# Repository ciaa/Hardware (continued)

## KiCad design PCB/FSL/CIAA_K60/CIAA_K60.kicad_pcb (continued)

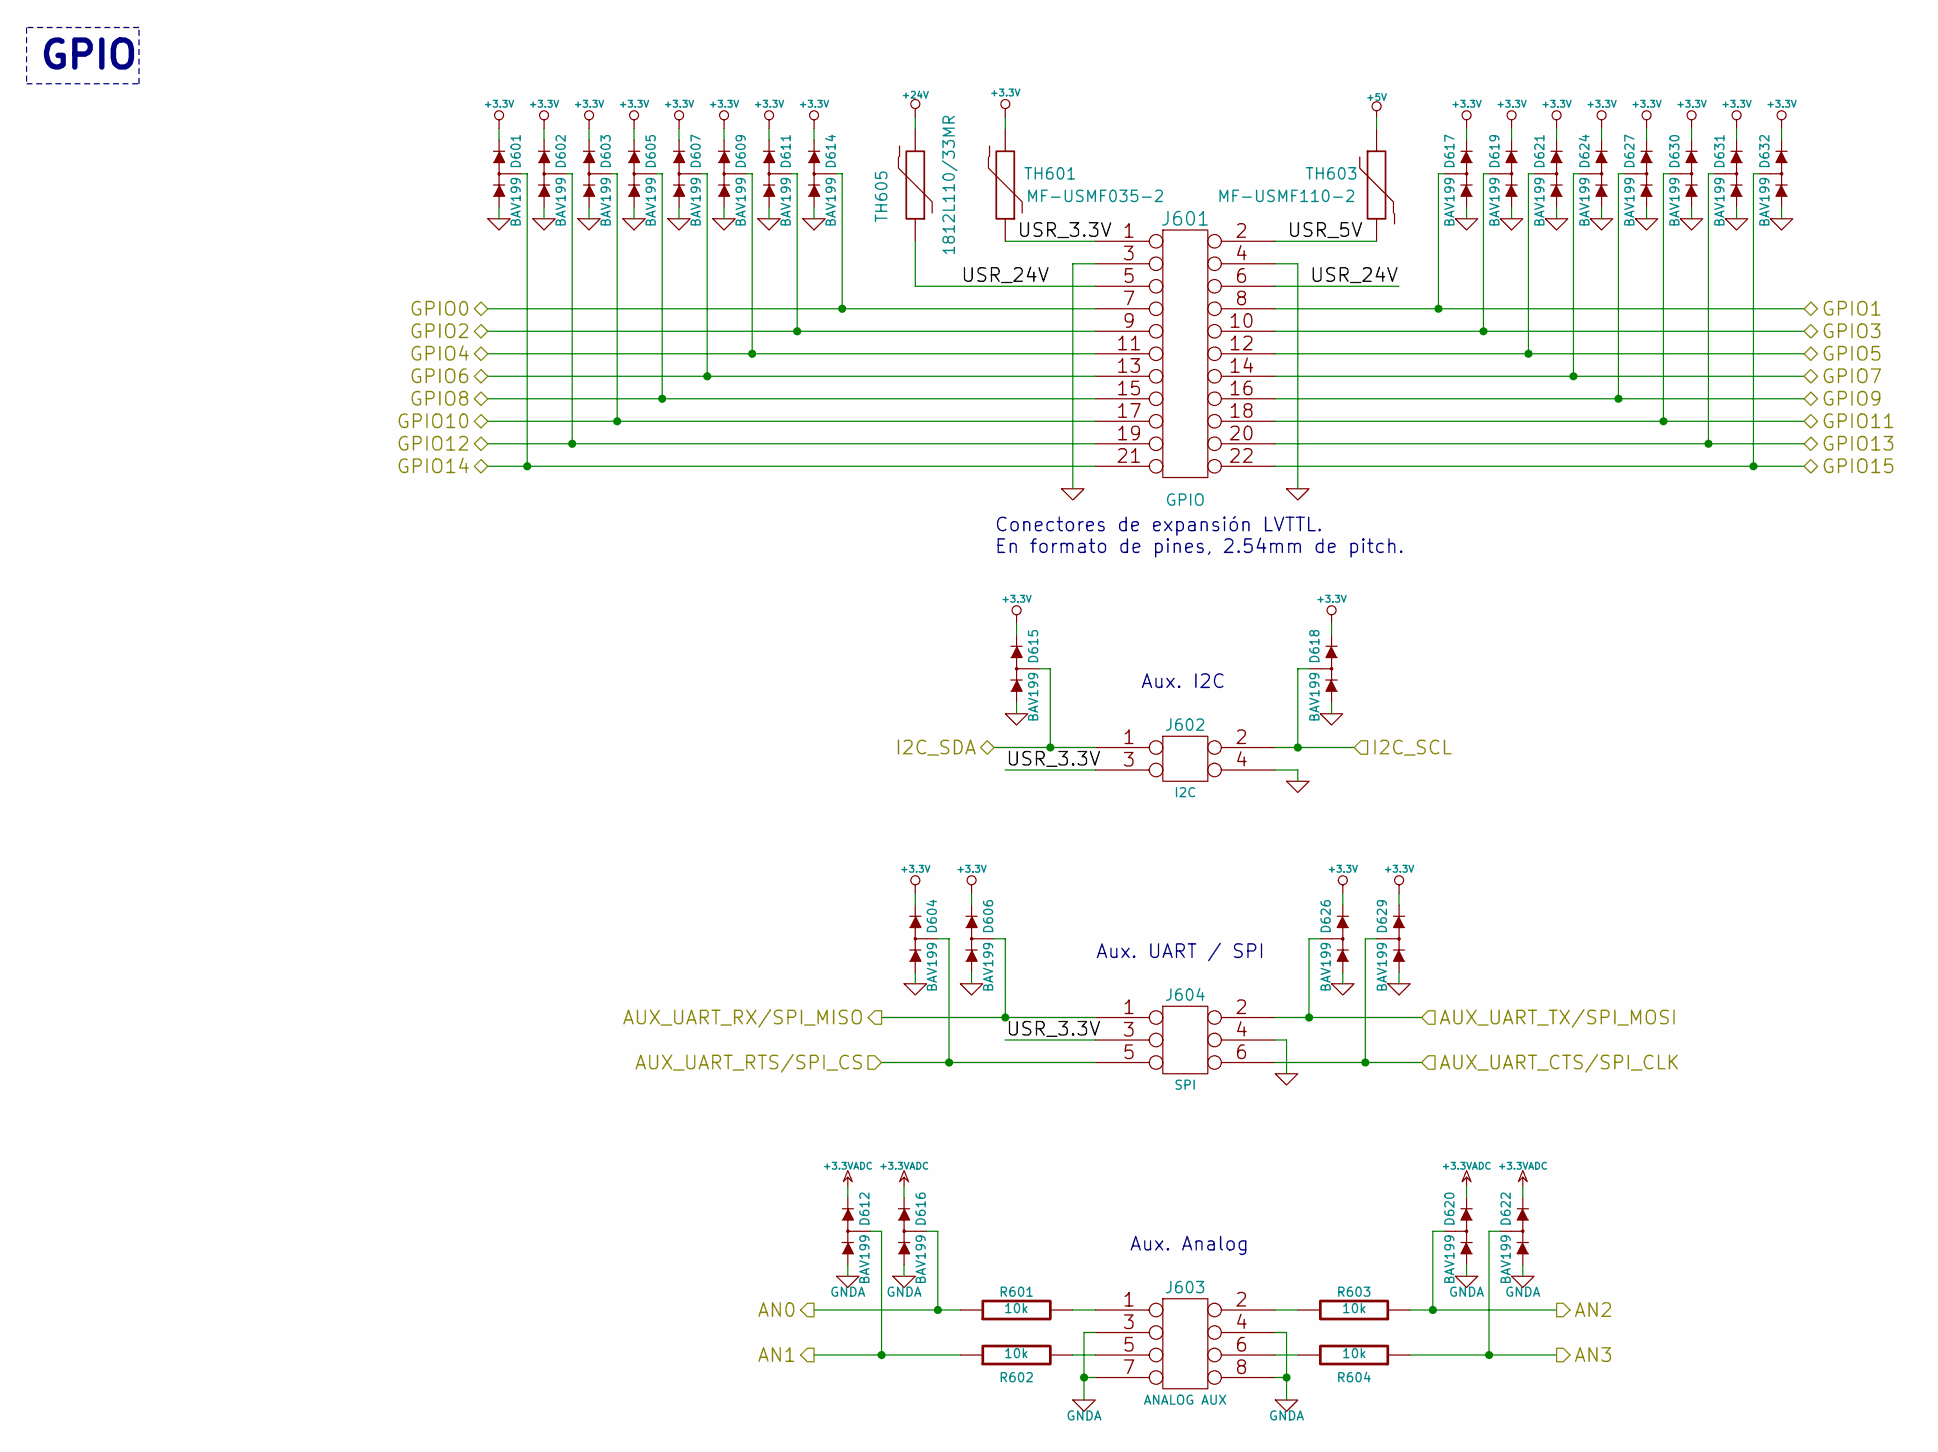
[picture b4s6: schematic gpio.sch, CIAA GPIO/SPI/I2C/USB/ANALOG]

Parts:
D601, D602, D603, D604, D605, D606, D607, D609, D611, D612, D614, D615, D616, D617, D618, D619, D620, D621, D622, D624, D626, D627, D629, D630, D631, D632: BAV199; SOT-23; Digikey# BAV199LT1GOSCT-ND
J601: GPIO; PIN_ARRAY_11x2; Digikey# S2012EC-40-ND
J602: I2C; PIN_ARRAY_2x2; Digikey# S2012EC-40-ND
J603: ANALOG AUX; PIN_ARRAY_4x2; Digikey# S2012EC-40-ND
J604: SPI; PIN_ARRAY_3x2; Digikey# S2012EC-40-ND
R601, R602, R603, R604: 10k; r_0603; Digikey# 311-10KGRCT-ND
TH601: MF-USMF035-2; ptc_1210; Digikey# MF-USMF035-2CT-ND
TH603: MF-USMF110-2; ptc_1210; Digikey# MF-USMF110-2CT-ND
TH605: 1812L110/33MR; ptc_1812; Digikey# F3486CT-ND

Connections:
+3.3VADC: D612.2 (K), D616.2 (K), D620.2 (K), D622.2 (K); also elsewhere on the board
+5V: TH603.1; also elsewhere on the board
+24V: TH605.2; also elsewhere on the board
/CPU/AUX_UART_CTS/SPI_CLK: D629.3 (KA), J604.6; also elsewhere on the board
/CPU/AUX_UART_RTS/SPI_CS: D604.3 (KA), J604.5; also elsewhere on the board
/CPU/AUX_UART_RX/SPI_MISO: D606.3 (KA), J604.1; also elsewhere on the board
/CPU/AUX_UART_TX/SPI_MOSI: D626.3 (KA), J604.2; also elsewhere on the board
/CPU/GPIO0: D614.3 (KA), J601.7; also elsewhere on the board
/CPU/GPIO1: D617.3 (KA), J601.8; also elsewhere on the board
/CPU/GPIO2: D611.3 (KA), J601.9; also elsewhere on the board
/CPU/GPIO3: D619.3 (KA), J601.10; also elsewhere on the board
/CPU/GPIO4: D609.3 (KA), J601.11; also elsewhere on the board
/CPU/GPIO5: D621.3 (KA), J601.12; also elsewhere on the board
/CPU/GPIO6: D607.3 (KA), J601.13; also elsewhere on the board
/CPU/GPIO7: D624.3 (KA), J601.14; also elsewhere on the board
/CPU/GPIO8: D605.3 (KA), J601.15; also elsewhere on the board
/CPU/GPIO9: D627.3 (KA), J601.16; also elsewhere on the board
/CPU/GPIO10: D603.3 (KA), J601.17; also elsewhere on the board
/CPU/GPIO11: D630.3 (KA), J601.18; also elsewhere on the board
/CPU/GPIO12: D602.3 (KA), J601.19; also elsewhere on the board
/CPU/GPIO13: D631.3 (KA), J601.20; also elsewhere on the board
/CPU/GPIO14: D601.3 (KA), J601.21; also elsewhere on the board
/CPU/GPIO15: D632.3 (KA), J601.22; also elsewhere on the board
/CPU/I2C_SCL: D618.3 (KA), J602.2; also elsewhere on the board
/CPU/I2C_SDA: D615.3 (KA), J602.1; also elsewhere on the board
/GPIO/AN0: D616.3 (KA), R601.1; also elsewhere on the board
/GPIO/AN1: D612.3 (KA), R602.1; also elsewhere on the board
/GPIO/AN2: D620.3 (KA), R603.1; also elsewhere on the board
/GPIO/AN3: D622.3 (KA), R604.1; also elsewhere on the board
/GPIO/USR_3.3V: J601.1, J602.3, J604.3, TH601.1
/GPIO/USR_5V: J601.2, TH603.2
/GPIO/USR_24V: J601.5, J601.6, TH605.1
GND: D601.1 (A), D602.1 (A), D603.1 (A), D604.1 (A), D605.1 (A), D606.1 (A), D607.1 (A), D609.1 (A), D611.1 (A), D614.1 (A), D615.1 (A), D617.1 (A), D618.1 (A), D619.1 (A), D621.1 (A), D624.1 (A), D626.1 (A), D627.1 (A), D629.1 (A), D630.1 (A), D631.1 (A), D632.1 (A), J601.3, J601.4, J602.4, J604.4; also elsewhere on the board
GNDA: D612.1 (A), D616.1 (A), D620.1 (A), D622.1 (A), J603.3, J603.4, J603.7, J603.8; also elsewhere on the board
unnamed: J603.1, R601.2
unnamed: J603.2, R603.2
unnamed: J603.5, R602.2
unnamed: J603.6, R604.2

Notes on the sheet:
Conectores de expansión LVTTL. En formato de pines, 2.54mm de pitch.
Aux. UART / SPI
GPIO
Aux. I2C
Aux. Analog

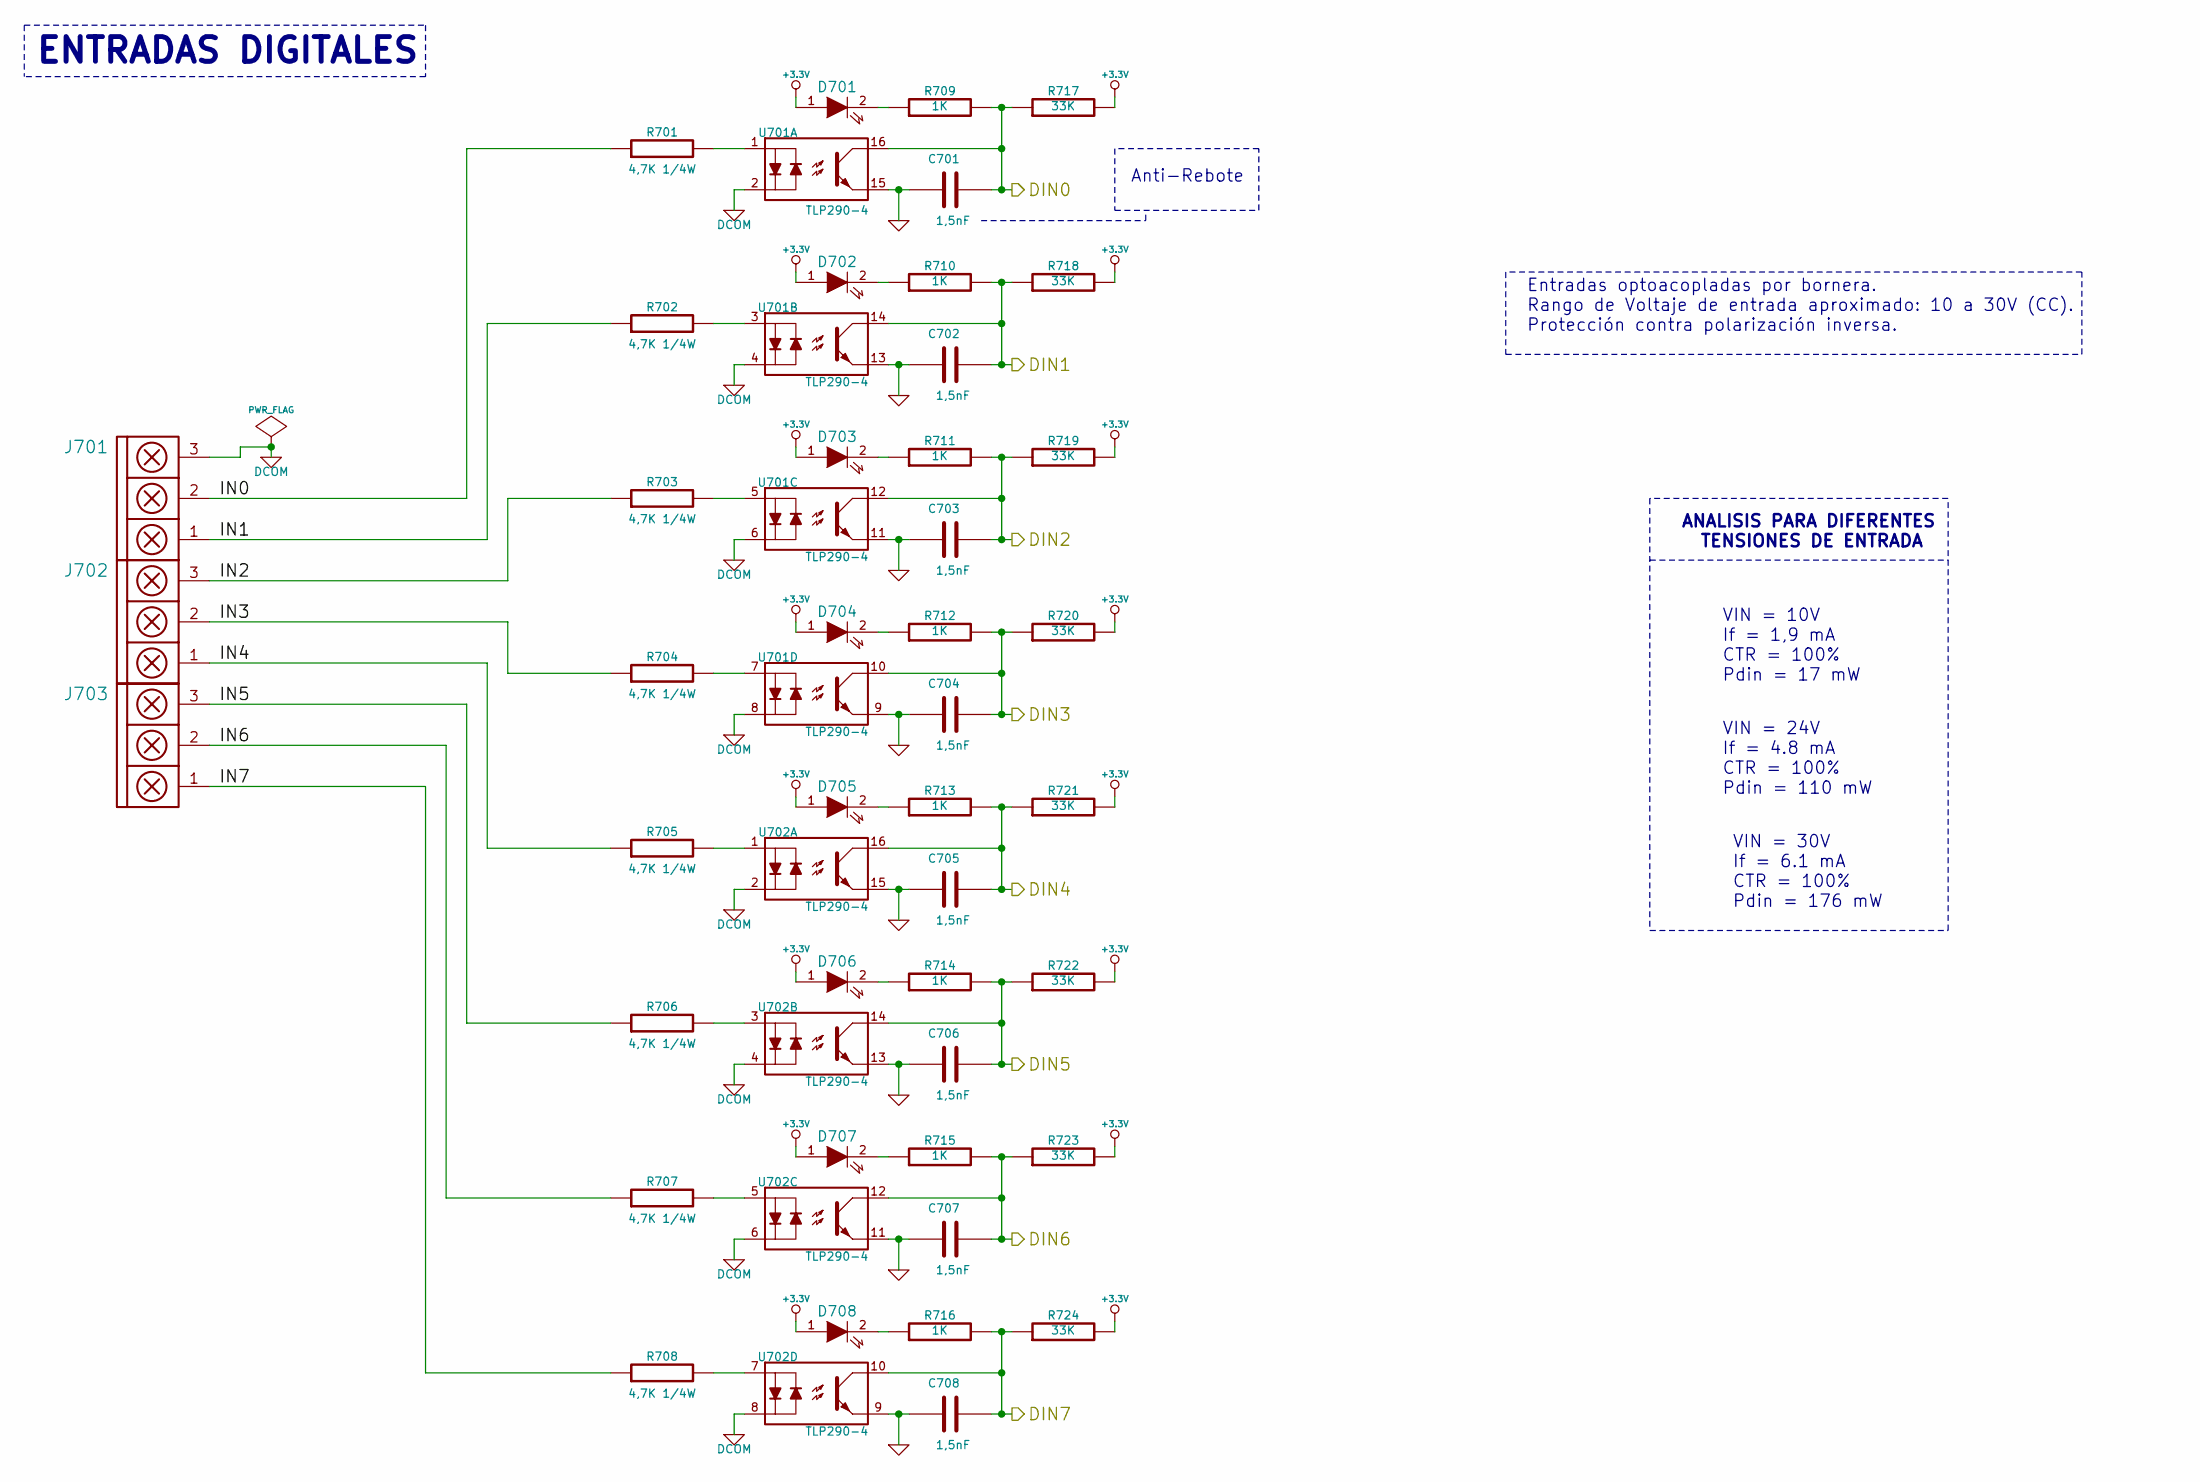
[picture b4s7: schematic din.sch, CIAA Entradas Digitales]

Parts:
C701, C702, C703, C704, C705, C706, C707, C708: 1,5nF; c_0603; Digikey# 399-1084-1-ND
D701, D702, D703, D704, D705, D706, D707, D708: LED red; LED-0603; Digikey# 1080-1400-1-ND
J701: DIG_INA; bornier3; Digikey# 571-7969493
J702: DIG_INB; bornier3; Digikey# 571-7969493
J703: DIG_INC; bornier3; Digikey# 571-7969493
R701, R702, R703, R704, R705, R706, R707, R708: 4,7K 1/4W; r_1206; Digikey# 311-4.7KERCT-ND
R709, R710, R711, R712, R713, R714, R715, R716: 1K; r_0603; Digikey# 311-1.0KGRCT-ND
R717, R718, R719, R720, R721, R722, R723, R724: 33K; r_0603; Digikey# 311-33KGRCT-ND
U701, U702: TLP290-4; SSOP-16; Digikey# TLP290-4(TPETR-ND

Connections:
/CPU/DIN0: C701.2, R709.2, R717.1, U701.16; also elsewhere on the board
/CPU/DIN1: C702.2, R710.2, R718.1, U701.14; also elsewhere on the board
/CPU/DIN2: C703.2, R711.2, R719.1, U701.12; also elsewhere on the board
/CPU/DIN3: C704.2, R712.2, R720.1, U701.10; also elsewhere on the board
/CPU/DIN4: C705.2, R713.2, R721.1, U702.16; also elsewhere on the board
/CPU/DIN5: C706.2, R714.2, R722.1, U702.14; also elsewhere on the board
/CPU/DIN6: C707.2, R715.2, R723.1, U702.12; also elsewhere on the board
/CPU/DIN7: C708.2, R716.2, R724.1, U702.10; also elsewhere on the board
/Entradas Digitales/IN0: J701.2, R701.1
/Entradas Digitales/IN1: J701.1, R702.1
/Entradas Digitales/IN2: J702.3, R703.1
/Entradas Digitales/IN3: J702.2, R704.1
/Entradas Digitales/IN4: J702.1, R705.1
/Entradas Digitales/IN5: J703.3, R706.1
/Entradas Digitales/IN6: J703.2, R707.1
/Entradas Digitales/IN7: J703.1, R708.1
DCOM: J701.3, U701.2, U701.4, U701.6, U701.8, U702.2, U702.4, U702.6, U702.8
GND: C701.1, C702.1, C703.1, C704.1, C705.1, C706.1, C707.1, C708.1, U701.9, U701.11, U701.13, U701.15, U702.9, U702.11, U702.13, U702.15; also elsewhere on the board
unnamed: R706.2, U702.3
unnamed: R705.2, U702.1
unnamed: D706.2 (K), R714.1
unnamed: D705.2 (K), R713.1
unnamed: D704.2 (K), R712.1
unnamed: R704.2, U701.7
unnamed: D708.2 (K), R716.1
unnamed: R708.2, U702.7
unnamed: D707.2 (K), R715.1
unnamed: R707.2, U702.5
unnamed: D701.2 (K), R709.1
unnamed: R701.2, U701.1
unnamed: D703.2 (K), R711.1
unnamed: R703.2, U701.5
unnamed: D702.2 (K), R710.1
unnamed: R702.2, U701.3

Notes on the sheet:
Entradas optoacopladas por bornera. Rango de Voltaje de entrada aproximado: 10 a 30V (CC). Protección contra polarización inversa.
ANALISIS PARA DIFERENTES TENSIONES DE ENTRADA
VIN = 10V If = 1,9 mA CTR = 100% Pdin = 17 mW
VIN = 24V If = 4.8 mA CTR = 100% Pdin = 110 mW
VIN = 30V If = 6.1 mA CTR = 100% Pdin = 176 mW
ENTRADAS DIGITALES
Anti-Rebote

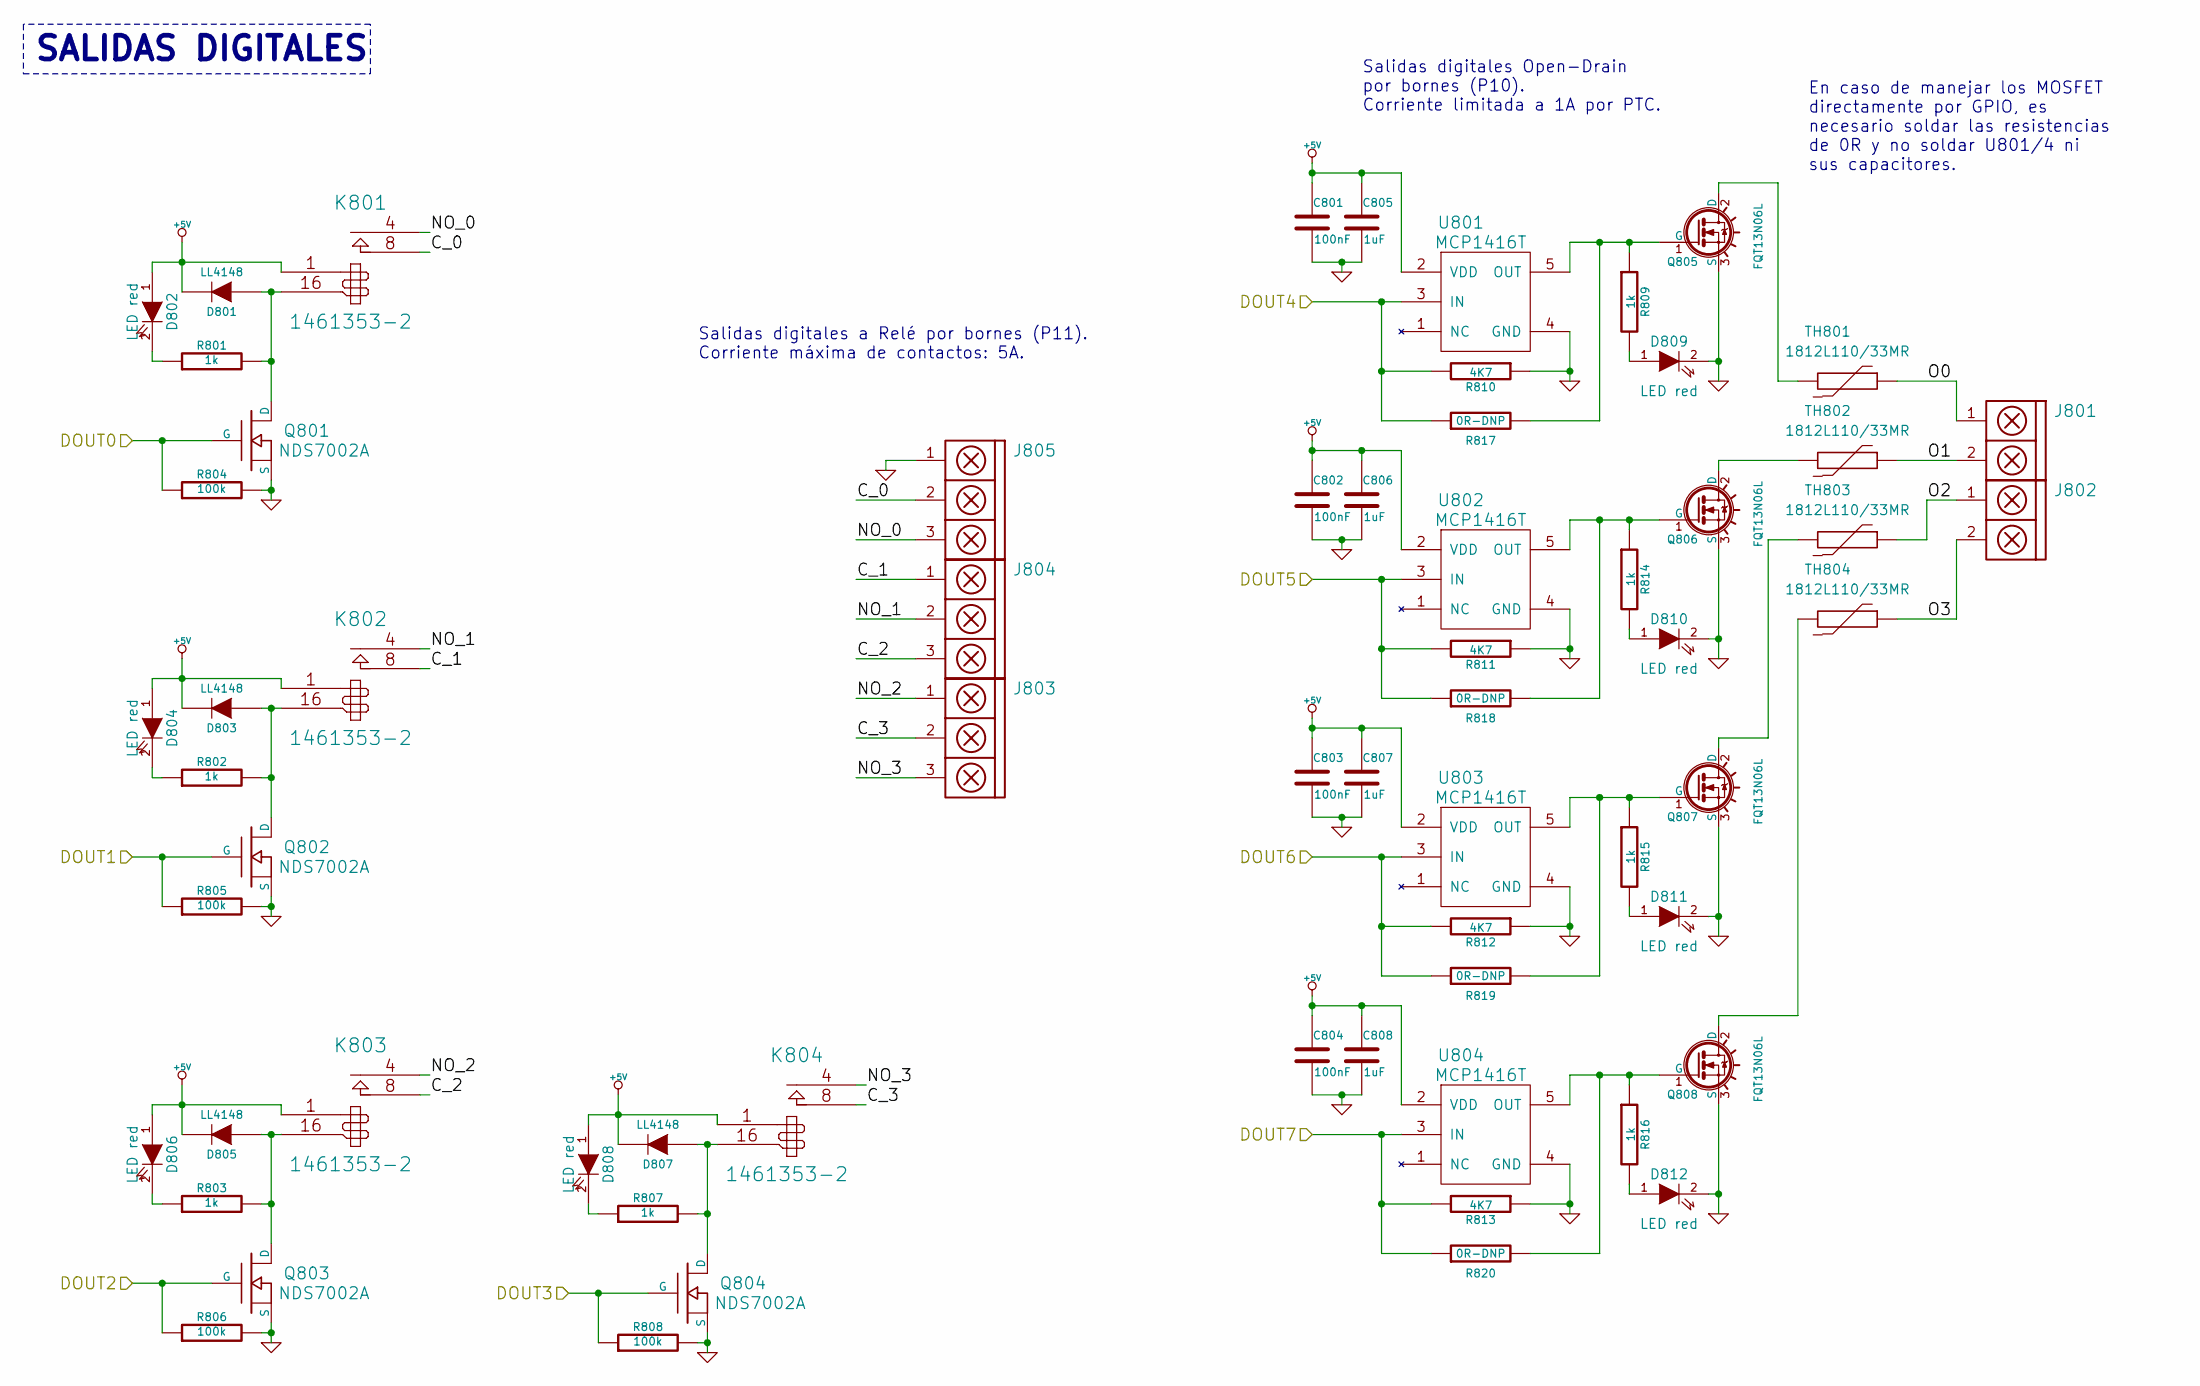
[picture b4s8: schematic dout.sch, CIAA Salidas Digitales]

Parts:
C801, C802, C803, C804: 100nF; c_0603; Digikey# 399-1096-1-ND
C805, C806, C807, C808: 1uF; c_0603; Digikey# 399-7847-1-ND
D801, D803, D805, D807: LL4148; SOD-123; Digikey# LL4148FSCT-ND
D802, D804, D806, D808, D809, D810, D811, D812: LED red; LED-0603; Digikey# 1080-1400-1-ND
J801: OPDRAIN_OUTA; bornier2; Digikey# 571-7969492
J802: OPDRAIN_OUTB; bornier2; Digikey# 571-7969492
J803: RELAY_OUTD; bornier3; Digikey# 571-7969493
J804, J805: RELAY_OUTB; bornier3; Digikey# 571-7969493
K801, K802, K803, K804: 1461353-2; Digikey# PB1652-ND
Q801, Q802, Q803, Q804: NDS7002A; SOT-23; Digikey# NDS7002ACT-ND
Q805, Q806, Q807, Q808: FQT13N06L; SOT-223; Digikey# FQT13N06LTFCT-ND
R801, R802, R803, R807, R809, R814, R815, R816: 1k; r_0603; Digikey# 311-1.0KGRCT-ND
R804, R805, R806, R808: 100k; r_0603; Digikey# 311-100KGRCT-ND
R810, R811, R812, R813: 4K7; r_0603; Digikey# 311-4.7KGRCT-ND
R817, R818, R819, R820: 0R-DNP; r_0603; Digikey# 311-0.0GRCT-ND
TH801, TH802, TH803, TH804: 1812L110/33MR; ptc_1812; Digikey# F3486CT-ND
U801, U802, U803, U804: MCP1416T; SOT-23-5; Digikey# MCP1416T-E/OTCT-ND

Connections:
+5V: C801.1, C802.1, C803.1, C804.1, C805.1, C806.1, C807.1, C808.1, D801.2 (K), D802.1 (A), D803.2 (K), D804.1 (A), D805.2 (K), D806.1 (A), D807.2 (K), D808.1 (A), K801.1, K802.1, K803.1, K804.1, U801.2 (VDD), U802.2 (VDD), U803.2 (VDD), U804.2 (VDD); also elsewhere on the board
/CPU/DOUT0: Q801.1 (G), R804.1; also elsewhere on the board
/CPU/DOUT1: Q802.1 (G), R805.1; also elsewhere on the board
/CPU/DOUT2: Q803.1 (G), R806.1; also elsewhere on the board
/CPU/DOUT3: Q804.1 (G), R808.1; also elsewhere on the board
/CPU/DOUT4: R810.2, R817.1, U801.3 (IN); also elsewhere on the board
/CPU/DOUT5: R811.2, R818.1, U802.3 (IN); also elsewhere on the board
/CPU/DOUT6: R812.2, R819.1, U803.3 (IN); also elsewhere on the board
/CPU/DOUT7: R813.2, R820.1, U804.3 (IN); also elsewhere on the board
/Salidas Digitales/C_0: J805.2, K801.8 (T1)
/Salidas Digitales/C_1: J804.1, K802.8 (T1)
/Salidas Digitales/C_2: J804.3, K803.8 (T1)
/Salidas Digitales/C_3: J803.2, K804.8 (T1)
/Salidas Digitales/NO_0: J805.3, K801.4 (C1)
/Salidas Digitales/NO_1: J804.2, K802.4 (C1)
/Salidas Digitales/NO_2: J803.1, K803.4 (C1)
/Salidas Digitales/NO_3: J803.3, K804.4 (C1)
/Salidas Digitales/O0: J801.1, TH801.1
/Salidas Digitales/O1: J801.2, TH802.1
/Salidas Digitales/O2: J802.1, TH803.1
/Salidas Digitales/O3: J802.2, TH804.1
GND: C801.2, C802.2, C803.2, C804.2, C805.2, C806.2, C807.2, C808.2, D809.2 (K), D810.2 (K), D811.2 (K), D812.2 (K), J805.1, Q801.2 (S), Q802.2 (S), Q803.2 (S), Q804.2 (S), Q805.3 (S), Q806.3 (S), Q807.3 (S), Q808.3 (S), R804.2, R805.2, R806.2, R808.2, R810.1, R811.1, R812.1, R813.1, U801.4 (GND), U802.4 (GND), U803.4 (GND), U804.4 (GND); also elsewhere on the board
unnamed: D809.1 (A), R809.2
unnamed: D811.1 (A), R815.2
unnamed: D810.1 (A), R814.2
unnamed: D812.1 (A), R816.2
unnamed: D803.1 (A), K802.16, Q802.3 (D), R802.2
unnamed: Q808.1 (G), R816.1, R820.2, U804.5 (OUT)
unnamed: Q805.1 (G), R809.1, R817.2, U801.5 (OUT)
unnamed: Q806.2 (D), TH802.2
unnamed: Q806.1 (G), R814.1, R818.2, U802.5 (OUT)
unnamed: Q807.1 (G), R815.1, R819.2, U803.5 (OUT)
unnamed: Q807.2 (D), TH803.2
unnamed: Q808.2 (D), TH804.2
unnamed: Q805.2 (D), TH801.2
unnamed: D801.1 (A), K801.16, Q801.3 (D), R801.2
unnamed: D802.2 (K), R801.1
unnamed: D804.2 (K), R802.1
unnamed: D807.1 (A), K804.16, Q804.3 (D), R807.2
unnamed: D805.1 (A), K803.16, Q803.3 (D), R803.2
unnamed: D806.2 (K), R803.1
unnamed: D808.2 (K), R807.1

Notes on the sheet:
Salidas digitales a Relé por bornes (P11). Corriente máxima de contactos: 5A.
SALIDAS DIGITALES
Salidas digitales Open-Drain por bornes (P10). Corriente limitada a 1A por PTC.
En caso de manejar los MOSFET directamente por GPIO, es necesario soldar las resistencias de 0R y no soldar U801/4 ni sus capacitores.

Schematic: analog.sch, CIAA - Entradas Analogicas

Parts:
C901, C902, C903, C904: 1nF; c_0603; Digikey# 399-1082-1-ND
C905, C906, C907, C908: 470pF; c_0603; Digikey# 399-1075-1-ND
C909: 10uF; c_1206POL; Digikey# 399-10116-1-ND
C910, C911, C912, C913, C914: 100nF; c_0603; Digikey# 399-1096-1-ND
D901, D902, D903, D904: BAV199; SOT-23; Digikey# BAV199LT1GOSCT-ND
D905, D906, D907, D908: P6SMB20CAT3G; DO-214AA_SMB; Digikey# P6SMB20CAT3GOSCT-ND
FB901, FB902, FB903, FB904: MMZ1608B601C; fb_0603; Digikey# 445-2166-1-ND
J901: ANALOG INPUT 1; bornier3; Digikey# 571-7969493
J902: ANALOG INPUT 2; bornier2; Digikey# 571-7969492
JP901, JP902, JP903, JP904: JUMPER; PIN_ARRAY_2x1
JP905, JP906, JP907, JP908: JUMPER3; PIN_ARRAY_3x1
R901, R902, R903, R904: 4.7; r_0603; Digikey# 311-4.7GRCT-ND
R905, R906, R907, R908: 237; r_0603; Digikey# P237DBCT-ND
R909, R910, R911, R912, R913, R914, R915, R916, R917, R918, R919, R920: 15k; r_0603; Digikey# RG16P15.0KBCT-ND
R921, R922, R923, R924: 100; r_0603; Digikey# 311-100GRCT-ND
U901: MCP6024; TSSOP-14; Digikey# MCP6024-I/ST-ND

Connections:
+3.3VADC: C909.1, C910.2, D901.2 (K), D902.2 (K), D903.2 (K), D904.2 (K), U901.4 (VDD); also elsewhere on the board
/CPU/AIN0: C911.2, R921.2; also elsewhere on the board
/CPU/AIN1: C912.2, R922.2; also elsewhere on the board
/CPU/AIN2: C913.2, R923.2; also elsewhere on the board
/CPU/AIN3: C914.2, R924.2; also elsewhere on the board
GNDA: C901.2, C902.2, C903.2, C904.2, C909.2, C910.1, C911.1, C912.1, C913.1, C914.1, D901.1 (A), D902.1 (A), D903.1 (A), D904.1 (A), D905.1, D906.1, D907.1, D908.1, J901.3, R901.1, R902.1, R903.1, R904.1, R905.1, R906.1, R907.1, R908.1, R914.1, R916.1, R918.1, R920.1, U901.11 (VSS); also elsewhere on the board
unnamed: JP907.1, R917.1, R918.2
unnamed: C907.1, FB903.2, JP903.2, R911.2
unnamed: JP907.3, R911.1, R917.2
unnamed: JP908.3, R912.1, R919.2
unnamed: JP906.1, R915.1, R916.2
unnamed: C903.1, D906.2, FB903.1, J902.2
unnamed: JP903.1, R907.2
unnamed: D903.3 (KA), JP907.2, U901.12 (+)
unnamed: D904.3 (KA), JP908.2, U901.10 (+)
unnamed: JP908.1, R919.1, R920.2
unnamed: JP904.1, R908.2
unnamed: C906.1, FB902.2, JP902.2, R910.2
unnamed: C908.1, FB904.2, JP904.2, R912.2
unnamed: R924.1, U901.8, U901.9 (-)
unnamed: R923.1, U901.13 (-), U901.14
unnamed: C905.2, R901.2
unnamed: C905.1, FB901.2, JP901.2, R909.2
unnamed: R921.1, U901.1, U901.2 (-)
unnamed: C902.1, D907.2, FB902.1, J901.1
unnamed: JP905.3, R909.1, R913.2
unnamed: JP905.1, R913.1, R914.2
unnamed: JP901.1, R905.2
unnamed: D901.3 (KA), JP905.2, U901.3 (+)
unnamed: D902.3 (KA), JP906.2, U901.5 (+)
unnamed: JP906.3, R910.1, R915.2
unnamed: JP902.1, R906.2
unnamed: C901.1, D908.2, FB901.1, J901.2
unnamed: C908.2, R904.2
unnamed: R922.1, U901.6 (-), U901.7
unnamed: C906.2, R902.2
unnamed: C907.2, R903.2
unnamed: C904.1, D905.2, FB904.1, J902.1

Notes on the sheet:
Filtro AF
Resistencia de Conversión I/V
Atenuador a 3.3V Fondo de Escala
Protección 3.3V
Buffer
Filtro Anti-aliasing fc: 16KHz
Protección
ENTRADAS ANALÓGICAS
Medición JUMPER JUMPER3 (SPDT)
TENSION (0-10)V Abierto 1-2
CORRIENTE (0-20)mA Cerrado 2-3

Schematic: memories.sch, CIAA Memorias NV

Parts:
C1001, C1002, C1003, C1005: 100nF; c_0603; Digikey# 399-1096-1-ND
C1004: 10uF; c_1206POL; Digikey# 399-10116-1-ND
D1001: SD CARD; LED-0603; Digikey# 1080-1399-1-ND
J1001: SD CARD; MicroSD_Hinged; Digikey# WM6698CT-ND
Q1001: FDN340P; SOT-23; Digikey# FDN340PCT-ND
R1001, R1002, R1003, R1004, R1005, R1006, R1007, R1014: 0R; r_0603; Digikey# 311-0.0GRCT-ND
R1008, R1010, R1011, R1012, R1013, R1015: 10k; r_0603; Digikey# 311-10KGRCT-ND
R1009: 750k; r_0603; Digikey# 311-750KGRCT-ND
R1016: 680; r_0603; Digikey# 311-680GRCT-ND
U1001: S25FL032P0XMFI013; SOIC-8_WIDE; Digikey# S25FL032P0XMFI013-ND
U1002: 24AA1025; SOIC-8; Digikey# 24AA1025-I/SN-ND
U1003: 24AA025E48; SOIC-8; Digikey# 24AA025E48-I/SN-ND

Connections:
/CPU/I2C_SCL: U1002.6 (SCL), U1003.6 (SCL); also elsewhere on the board
/CPU/I2C_SDA: U1002.5 (SDA), U1003.5 (SDA); also elsewhere on the board
/CPU/SD_CLK: J1001.5 (CLK); also elsewhere on the board
/CPU/SD_CMD: J1001.3 (CMD), R1010.2; also elsewhere on the board
/CPU/SD_DAT0: J1001.7 (DAT0), R1012.2; also elsewhere on the board
/CPU/SD_DAT1: J1001.8 (DAT1), R1013.2; also elsewhere on the board
/CPU/SD_DAT2: J1001.1 (DAT2), R1008.2; also elsewhere on the board
/CPU/SD_DAT3: J1001.2 (CD/DAT3), R1009.1; also elsewhere on the board
/CPU/SD_POW: Q1001.1 (G), R1011.2; also elsewhere on the board
/CPU/SPIFI_CLK: U1001.6 (CLK); also elsewhere on the board
/CPU/SPIFI_CS: U1001.1 (nCS); also elsewhere on the board
/CPU/SPIFI_HOLD: U1001.7 (nHOLD/IO3); also elsewhere on the board
/CPU/SPIFI_MISO: U1001.2 (DO/IO1); also elsewhere on the board
/CPU/SPIFI_MOSI: U1001.5 (DI/IO0); also elsewhere on the board
/CPU/SPIFI_WP: U1001.3 (nWP/IO2); also elsewhere on the board
GND: C1001.2, C1002.2, C1003.2, C1004.2, C1005.2, D1001.2 (K), J1001.6 (VSS), J1001.9 (SHLD1), J1001.10 (SHLD2), J1001.11 (SHLD3), J1001.12 (SHLD4), R1001.2, R1002.2, R1004.2, R1006.2, R1007.2, R1009.2, R1014.2, R1015.2, U1001.4 (GND), U1002.4 (GND), U1003.4 (GND); also elsewhere on the board
unnamed: R1014.1, U1003.7 (WP)
unnamed: R1005.2, U1003.1 (A0)
unnamed: R1004.1, U1002.7 (WP)
unnamed: D1001.1 (A), R1016.2
unnamed: R1003.1, U1002.3 (A2)
unnamed: R1002.1, U1002.2 (A1)
unnamed: R1001.1, U1002.1 (A0)
unnamed: R1007.1, U1003.3 (A2)
unnamed: R1006.1, U1003.2 (A1)
unnamed: C1004.1, C1005.1, J1001.4 (VDD), Q1001.3 (D), R1008.1, R1010.1, R1012.1, R1013.1, R1015.1, R1016.1

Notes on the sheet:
EEPROM, 1Mbit
EEPROM, 2kbit EUI-48 Node Identity
Flash QSPI, 32Mbit
Micro SD Card
MEMORIAS NV
Detección de la memoria: Como el zócalo no posee switch mecánico, se utiliza un cambio de nivel en la línea DAT3, para lo cual es necesario un pull down (el valor 750k es el recomendado por FSL).

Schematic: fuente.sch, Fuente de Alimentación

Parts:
BT1101: CR2032; 2032batPTH; Digikey# BH32T-C-ND
C1101: 470uF; c_elec_10x13_5; Digikey# 493-3961-1-ND
C1102: 330uF; c_elec_8x10; Digikey# 493-9422-1-ND
C1103: 10uF; c_1206POL; Digikey# 399-10116-1-ND
C1104, C1106: 100nF; c_0603; Digikey# 399-1096-1-ND
C1105: 100nF; c_0603; Digikey# 1276-1936-1-ND
D1101, D1109: MURS360; DO-214AB_SMC; Digikey# MURS360T3GOSCT-ND
D1102: MBRS540T3G; DO-214AB_SMC; Digikey# MBRS540T3GOSCT-ND
D1103, D1104: MBRS130LT3G; DO-214AA_SMB; Digikey# MBRS130LT3GOSCT-ND
D1105: LED +5V; LED-0603; Digikey# 1080-1400-1-ND
D1106: MMSZ5V6T1G; SOD-123; Digikey# MMSZ5V6T1GOSCT-ND
D1107: P6SMB33CA; DO-214AA_SMB; Digikey# P6SMB33CA-E3/52GICT-ND
D1108: BAT54C; SOT-23; Digikey# BAT54FSCT-ND
FB1101, FB1102: MMZ1608B601C; fb_0603; Digikey# 445-2166-1-ND
J1101: DC-INPUT; bornier3; Digikey# 571-7969493
J1102: DC-OUT; bornier2; Digikey# 571-7969492
L1101: 47uH; L_10x9.8_SMD; Digikey# SRN1060-470MCT-ND
R1101: 1k; r_0603; Digikey# 311-1.0KGRCT-ND
TH1101: MF-SM300; Digikey# MF-SM300-2CT-ND
TH1102: 1812L110/33MR; ptc_1812; Digikey# F3486CT-ND
TP1101, TP1102: TESTPOINT_PDN
U1101: LM2596-5.0; LM2596; Digikey# LM2596SX-5.0/NOPBCT-ND
U1102: NCP1117ST33T3G; SOT-223; Digikey# NCP1117ST33T3GOSCT-ND

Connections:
+3.3VADC: FB1101.2; also elsewhere on the board
+5V: C1102.1, C1106.1, D1103.2 (K), D1104.2 (K), D1106.2 (K), L1101.2, R1101.1, U1101.4 (FB), U1102.3 (VI); also elsewhere on the board
+24V: D1101.2 (K), TH1101.1; also elsewhere on the board
+VIN: D1109.2 (K), TH1102.2
/CPU/VBAT: C1104.1, D1108.3 (C); also elsewhere on the board
/Fuente/USB_VBUS: D1103.1 (A); also elsewhere on the board
/JTAG/USB_DEBUG_VBUS: D1104.1 (A); also elsewhere on the board
GND: BT1101.2 (-), C1101.2, C1102.2, C1103.2, C1104.2, C1105.2, C1106.2, D1102.1 (A), D1105.2 (K), D1106.1 (A), D1107.2, FB1102.1, J1101.2, J1102.2, TP1101.2, TP1102.2, U1101.3 (GND), U1101.5 (~ON~/OFF), U1102.1 (GND); also elsewhere on the board
GNDA: FB1102.2; also elsewhere on the board
GNDPWR: J1101.1; also elsewhere on the board
unnamed: C1101.1, C1105.1, D1107.1, TH1101.2, U1101.1 (IN)
unnamed: D1102.2 (K), L1101.1, U1101.2 (OUT)
unnamed: BT1101.1 (+), D1108.1 (B)
unnamed: J1102.1, TH1102.1
unnamed: D1105.1 (A), R1101.2
unnamed: D1101.1 (A), D1109.1 (A), J1101.3

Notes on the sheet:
Polyswitch
Reemplazo SMD del 1N5825.
Ferrite separador de alimentación digital de analógica
FUENTE DE ALIMENTACIÓN
DC INPUT: 12 a 30V CC
REGULADOR: 5V 3A
REGULADOR: 3.3V 1A
Alimentación alternativa por: USB-DEBUG y USB-OTG
PILA
DC OUTPUT: Max. 1A
TESTPOINTS PARA PDN

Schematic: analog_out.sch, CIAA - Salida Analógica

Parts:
C1201: 100nF; c_0603; Digikey# 1276-1936-1-ND
C1202: 10nF; c_0603; Digikey# 399-1091-1-ND
D1201, D1202: BAV199; SOT-23; Digikey# BAV199LT1GOSCT-ND
FB1201: MMZ1608B601C; fb_0603; Digikey# 445-2166-1-ND
J1201: ANALOG OUT; bornier2; Digikey# 571-7969492
JP1201: JUMPER3; PIN_ARRAY_3x1; Digikey# S1212EC-40-ND
Q1201: BC817-40; SOT-23; Digikey# BC817-40LT3GOSCT-ND
Q1202: PBSS5240XF; SOT-89; Digikey# 568-10522-1-ND
R1201: 15k; r_0603; Digikey# RG16P15.0KBCT-ND
R1202: 33k; r_0603; Digikey# RG16P33.0KBCT-ND
R1203: 2.49k; r_0603; Digikey# RG16P2.49KBCT-ND
R1204: 2.2k; r_0603; Digikey# 311-2.2KGRCT-ND
R1205: 24.9; r_0603; Digikey# RT0603BRD0724R9L-ND
R1206: 10K; r_0603; Digikey# 311-10KGRCT-ND
TH1201: MF-USMF005-2; ptc_1210; Digikey# MF-USMF005-2CT-ND
U1201: LM358DG; SOIC-8; Digikey# LM358DGOS-ND

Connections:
+24V: FB1201.1; also elsewhere on the board
+24V_A: C1201.1, D1201.1 (A), D1202.2 (K), FB1201.2, U1201.8 (V+)
/CPU/DAC_OUT: U1201.5 (+); also elsewhere on the board
GNDA: C1201.2, C1202.1, D1202.1 (A), J1201.1, R1201.1, R1206.1, U1201.4 (V-); also elsewhere on the board
unnamed: Q1202.3 (B), U1201.1
unnamed: Q1202.1 (E), R1205.2, U1201.2 (-)
unnamed: Q1201.2 (E), R1204.2
unnamed: C1202.2, JP1201.3, Q1202.2 (C)
unnamed: J1201.2, TH1201.2
unnamed: R1201.2, R1202.2, U1201.6 (-)
unnamed: D1202.3 (KA), JP1201.2, TH1201.1
unnamed: JP1201.1, R1202.1, R1204.1
unnamed: Q1201.1 (B), U1201.7
unnamed: Q1201.3 (C), R1203.1, U1201.3 (+)
unnamed: D1201.2 (K), R1203.2, R1205.1, R1206.2

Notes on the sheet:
SALIDA ANALÓGICA
Filtro Fuente de 24V
Ganancia de Tensión dada por: 1+ R1202/R1201 = 3.2
Relación de conversión V/I Io=(DAC_OUT/R1201)*(R1203/R1205)
SALIDA JP1201
Corriente (4-20)mA 2-3
Tensión (0-10)V 1-2

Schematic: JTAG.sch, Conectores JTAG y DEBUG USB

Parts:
C1301, C1302, C1305, C1306, C1307, C1311, C1312, C1313, C1314, C1315, C1316, C1317, C1318, C1319: 100nF; c_0603; Digikey# 399-1096-1-ND
C1303, C1308, C1309, C1310: 4,7uF; c_1206POL; Digikey# 399-9717-1-ND
FB1301, FB1302, FB1303: MMZ1608B601C; fb_0603; Digikey# 445-2166-1-ND
FB1304: BLM18KG221SN1D; fb_0603; Digikey# 490-5255-1-ND
J1302: JTAG DEBUG USB; USB_MicroAB; Digikey# H11634CT-ND
J1303: JTAG DIRECTO; PIN_ARRAY_5x2_1.27_SMD; Digikey# 952-1389-ND
R1301, R1309, R1310, R1311: 10K; r_0603; Digikey# 311-10KGRCT-ND
R1302: 100; r_0603; Digikey# 311-100GRCT-ND
R1303: 12K 1%; r_0603; Digikey# 311-12.0KHRCT-ND
R1304: 1K; r_0603; Digikey# 311-1.0KGRCT-ND
R1312: 2K2; r_0603; Digikey# 311-2.2KGRCT-ND
TR1301: SRF2012; Digikey# SRF2012-900YCT-ND
U1301: 74HC244; TSSOP-20; Digikey# 568-8285-5-ND
U1302: FT2232H; TQFP64; Digikey# 768-1024-1-ND
U1303: 93C56; SOIC-8; Digikey# AT93C46DN-SH-B-ND
U1304: PRTR5V0U2X; SOT-143-4; Digikey# 568-4140-1-ND
U1305: SI501; SI501_C; Digikey# 336-2889-ND

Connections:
+USB_JTAG_1V8: C1303.1, C1305.1, C1311.1, C1312.1, C1313.1, U1302.12 (VCORE), U1302.37 (VCORE), U1302.49 (VREGOUT), U1302.64 (VCORE)
/CPU/RESET: J1303.10, U1301.12 (1Y4); also elsewhere on the board
/CPU/TCK: J1303.4, U1301.18 (1Y1); also elsewhere on the board
/CPU/TDI: J1303.8, U1301.16 (1Y2); also elsewhere on the board
/CPU/TDO: J1303.6, U1301.15 (2A3); also elsewhere on the board
/CPU/TMS: J1303.2, U1301.14 (1Y3); also elsewhere on the board
/CPU/USB_JTAG_UART_RXD: U1302.38 (BDBUS0); also elsewhere on the board
/CPU/USB_JTAG_UART_TXD: U1302.39 (BDBUS1); also elsewhere on the board
/JTAG/CHS_DBG: FB1303.2, J1302.6 (S2), J1302.7 (S1), J1302.8 (S3), J1302.9 (S4), U1304.1 (GND)
/JTAG/EECLK: R1310.2, U1302.62 (EECLK), U1303.2 (SK)
/JTAG/EECS: R1309.2, U1302.63 (EECS), U1303.1 (CS)
/JTAG/EEDATA: R1312.1, U1302.61 (EEDATA), U1303.3 (DI)
/JTAG/FT_OE: R1301.1, U1301.1 (1~OE), U1302.28 (ACBUS2)
/JTAG/FT_RST: U1301.8 (1A4), U1302.27 (ACBUS1)
/JTAG/FT_TCK: U1301.2 (1A1), U1302.16 (ADBUS0)
/JTAG/FT_TDI: U1301.4 (1A2), U1302.17 (ADBUS1)
/JTAG/FT_TDO: U1301.5 (2Y3), U1302.18 (ADBUS2)
/JTAG/FT_TMS: U1301.6 (1A3), U1302.19 (ADBUS3)
/JTAG/USB_DEBUG_VBUS: C1310.1, C1319.1, FB1304.2; also elsewhere on the board
/JTAG/USB_JTAG_DM: TR1301.3, U1302.7 (DM), U1304.3 (I/O)
/JTAG/USB_JTAG_DP: TR1301.2, U1302.8 (DP), U1304.2 (I/O)
GND: C1301.2, C1302.2, C1303.2, C1305.2, C1306.2, C1307.2, C1308.2, C1309.2, C1310.2, C1311.2, C1312.2, C1313.2, C1314.2, C1315.2, C1316.2, C1317.2, C1318.2, C1319.2, FB1303.1, J1302.5 (GND), J1303.3, J1303.5, J1303.9, R1303.1, U1301.10 (VSS), U1301.11 (2A1), U1301.13 (2A2), U1301.17 (2A4), U1301.19 (2~OE), U1302.1 (GND), U1302.5 (GND), U1302.10 (AGND), U1302.11 (GND), U1302.13 (TEST), U1302.15 (GND), U1302.25 (GND), U1302.35 (GND), U1302.47 (GND), U1302.51 (GND), U1303.5 (GND), U1305.2 (GND); also elsewhere on the board
unnamed: R1311.2, R1312.2, U1303.4 (DO)
unnamed: R1303.2, U1302.6 (REF)
unnamed: R1304.2, U1302.14 (~RESET)
unnamed: C1306.1, C1308.1, FB1301.2, U1302.9 (VPLL)
unnamed: C1307.1, C1309.1, FB1302.2, U1302.4 (VPHY)
unnamed: R1302.1, U1305.3 (OUT)
unnamed: R1302.2, U1302.2 (OSCI)
unnamed: FB1304.1, J1302.1 (VBUS), U1304.4 (VCC)
unnamed: J1302.3 (USB_DP), TR1301.1
unnamed: J1302.2 (USB_DN), TR1301.4

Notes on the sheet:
JTAG
EEPROM
JTAG DEBUG USB
ORG = VCC: 64 x 16 bits
Channel A: MPSSE
Channel B: ASYNC Serial
Pin ACBUS2 (FT_OE): default tri-stated input with an internal 75KΩ pull up resistor to VCCIO.
The external EEPROM can be used to customise the USB VID, PID, Serial Number, Product Description Strings and Power Descriptor
OSC. 12MHz

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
